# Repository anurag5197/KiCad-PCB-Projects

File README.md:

# KiCad PCB Projects — Anurag Kumar Gupta

A collection of PCB designs created in KiCad as part of my 
electronics engineering coursework and self-learning.

## Projects

### Motor Driver — DRV8833
Dual H-bridge motor driver PCB with PWM control, fault monitoring,
and thermally optimized layout using ground planes and thermal vias.

### USB to UART Converter
USB Type-C to UART converter using CP2102 IC for serial communication
between PC and embedded devices. 36 nets, fully routed.

### DC-DC Boost Converter
Boost converter PCB for stepping up DC voltage. Fully routed,
fabrication-ready design.

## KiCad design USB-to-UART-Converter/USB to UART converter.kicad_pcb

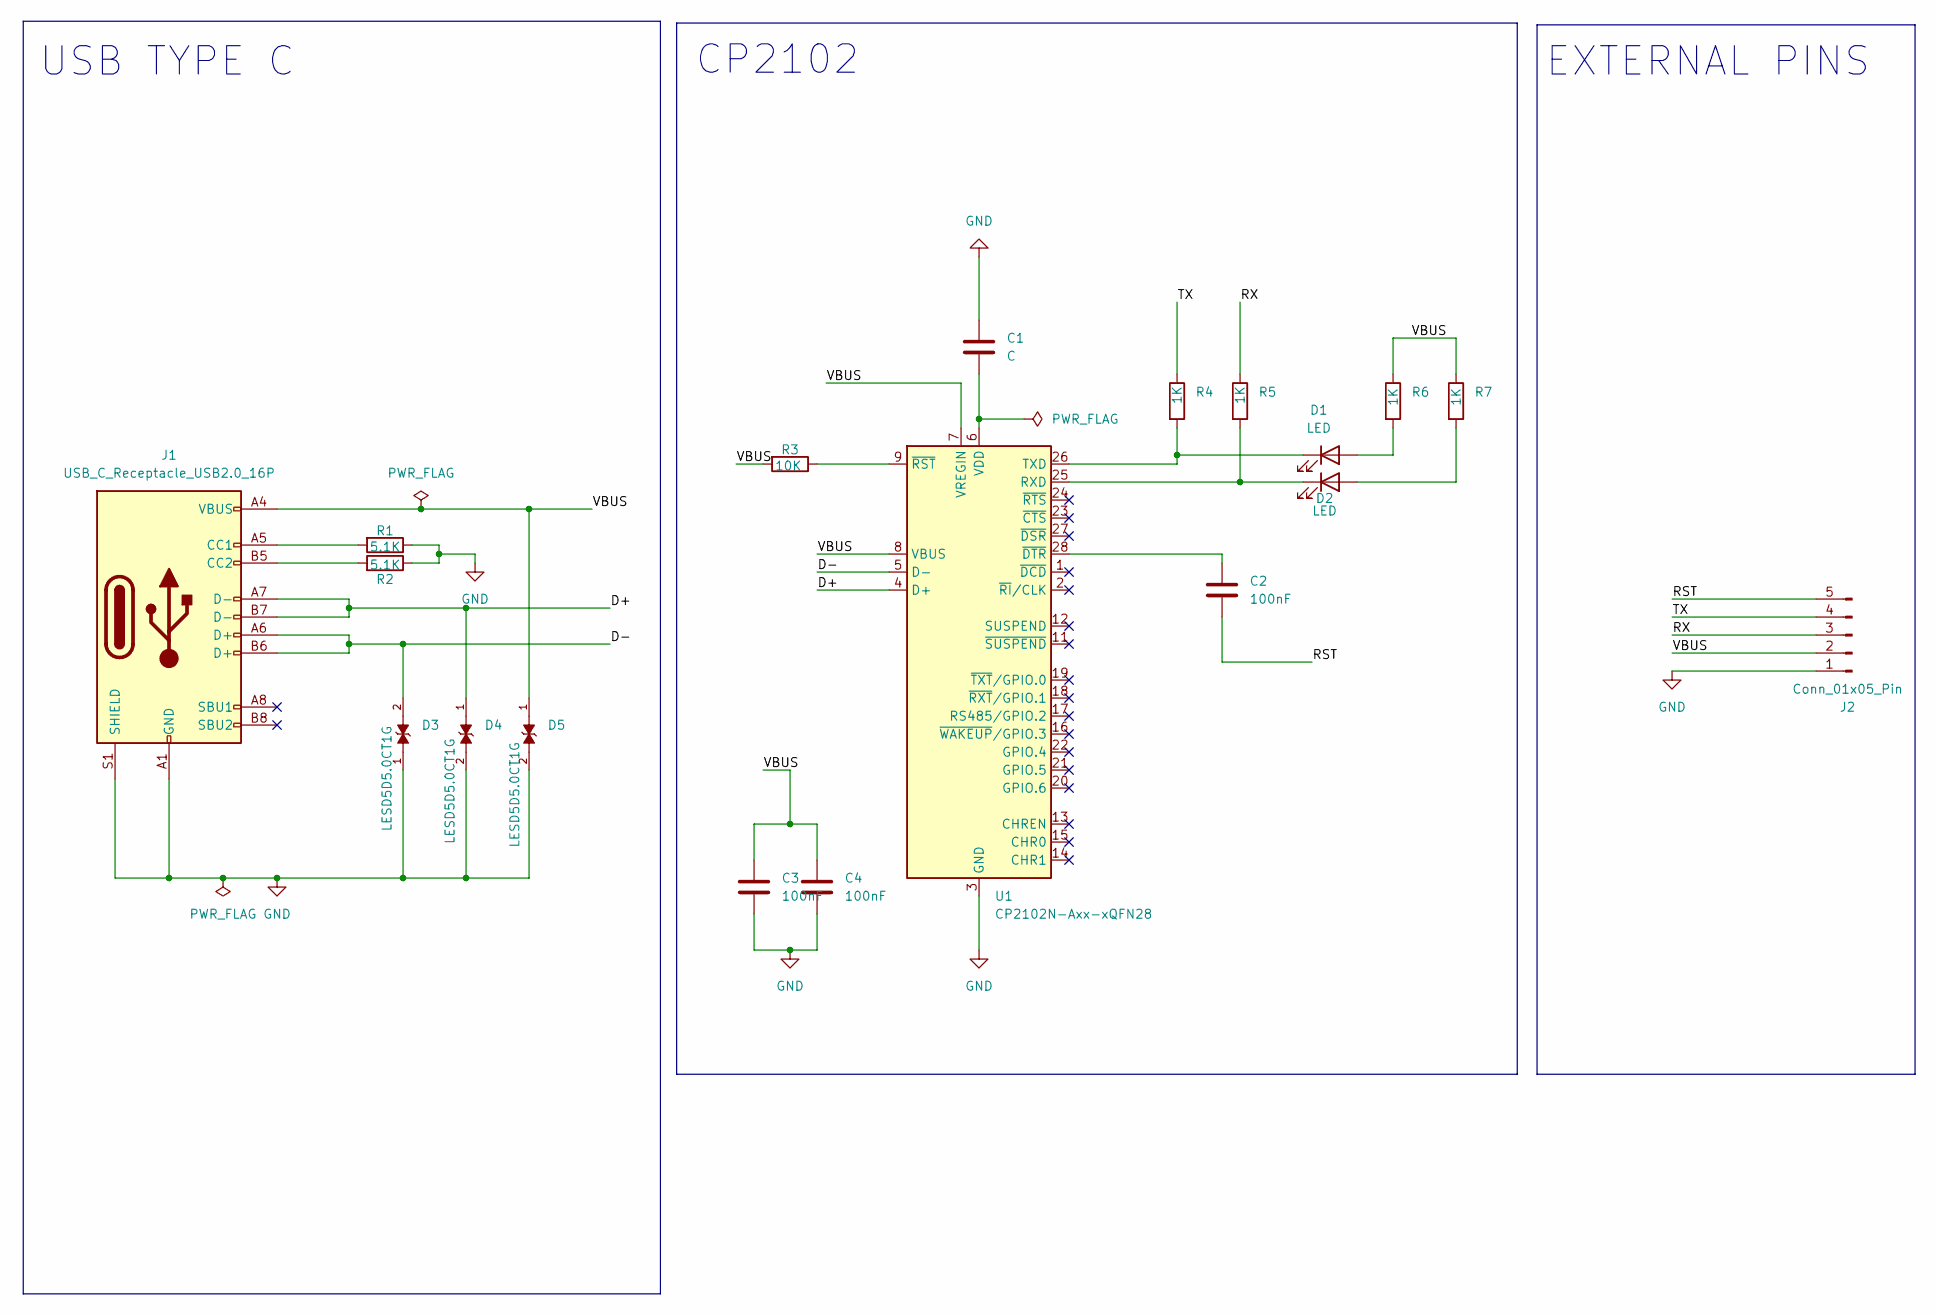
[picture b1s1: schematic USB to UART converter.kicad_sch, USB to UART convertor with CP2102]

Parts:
C1: C; C_0201_0603Metric
C2, C3, C4: 100nF; C_0201_0603Metric
D1, D2: LED; LED_0201_0603Metric
D3, D4, D5: LESD5D5.0CT1G; TVS_LESD5D5.0CT1G; PARTREV O
J1: USB_C_Receptacle_USB2.0_16P; USB_C_Receptacle_HRO_TYPE-C-31-M-12
J2: Conn_01x05_Pin; PinHeader_1x05_P2.54mm_Vertical
R1, R2: 5.1K; R_0201_0603Metric
R3: 10K; R_0201_0603Metric
R4, R5, R6, R7: 1K; R_0201_0603Metric
U1: CP2102N-Axx-xQFN28; QFN-28-1EP_5x5mm_P0.5mm_EP3.35x3.35mm

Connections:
/D+: D4.1, J1.A7 (D-), J1.B7 (D-), U1.4 (D+)
/D-: D3.2, J1.A6 (D+), J1.B6 (D+), U1.5 (D-)
/RST: C2.2, J2.5
/RX: J2.3, R5.1
/TX: J2.4, R4.1
/VBUS: C3.1, C4.1, D5.1, J1.A4 (VBUS), J1.A9 (VBUS), J1.B4 (VBUS), J1.B9 (VBUS), J2.2, R3.2, R6.1, R7.1, U1.7 (VREGIN), U1.8 (VBUS)
GND: C1.1, C3.2, C4.2, D3.1, D4.2, D5.2, J1.A1 (GND), J1.A12 (GND), J1.B1 (GND), J1.B12 (GND), J1.S1 (SHIELD), J2.1, R1.1, R2.1, U1.3 (GND), U1.29 (GND)
unnamed: D1.2 (A), R6.2
unnamed: D1.1 (K), R4.2, U1.26 (TXD)
unnamed: D2.2 (A), R7.2
unnamed: D2.1 (K), R5.2, U1.25 (RXD)
unnamed: J1.A5 (CC1), R1.2
unnamed: J1.B5 (CC2), R2.2
unnamed: C1.2, U1.6 (VDD)
unnamed: C2.1, U1.28 (~DTR)
unnamed: R3.1, U1.9 (~RST)

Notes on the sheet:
CP2102
USB TYPE C
EXTERNAL PINS

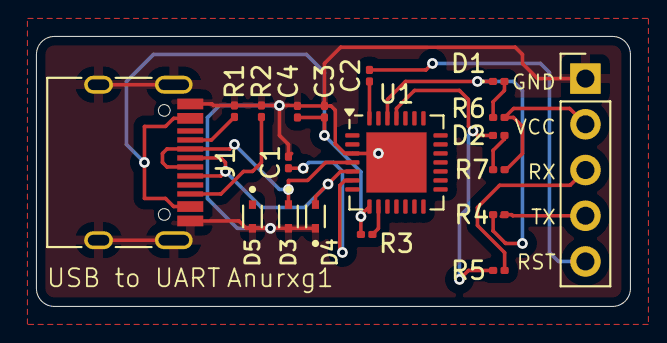
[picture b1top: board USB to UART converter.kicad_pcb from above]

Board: 2 copper layers, 33.0 x 15.0 mm, 19 parts (0 on the bottom side), 16 nets.

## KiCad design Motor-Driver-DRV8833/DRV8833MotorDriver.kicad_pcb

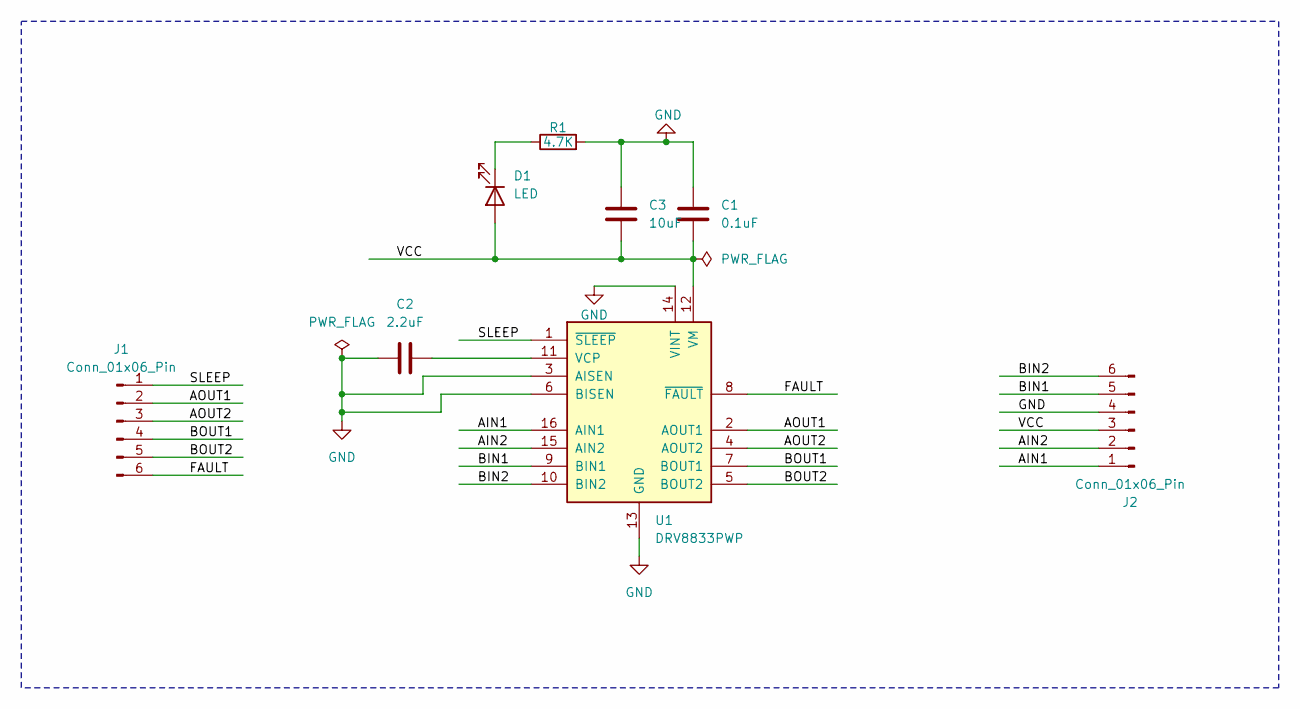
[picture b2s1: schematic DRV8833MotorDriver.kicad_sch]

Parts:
C1: 0.1uF; C_0805_2012Metric
C2: 2.2uF; C_0805_2012Metric
C3: 10uF; CP_EIA-6032-20_AVX-F
D1: LED; LED_0805_2012Metric
J1, J2: Conn_01x06_Pin; PinHeader_1x06_P2.54mm_Vertical
R1: 4.7K; R_0805_2012Metric
U1: DRV8833PWP; HTSSOP-16-1EP_4.4x5mm_P0.65mm_EP3.4x5mm_Mask2.46x2.31mm_The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

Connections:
/AIN1: J2.1, U1.16 (AIN1)
/AIN2: J2.2, U1.15 (AIN2)
/AOUT1: J1.2, U1.2 (AOUT1)
/AOUT2: J1.3, U1.4 (AOUT2)
/BIN1: J2.5, U1.9 (BIN1)
/BIN2: J2.6, U1.10 (BIN2)
/BOUT1: J1.4, U1.7 (BOUT1)
/BOUT2: J1.5, U1.5 (BOUT2)
/FAULT: J1.6, U1.8 (~FAULT)
/SLEEP: J1.1, U1.1 (~SLEEP)
/VCC: C1.2, C3.2, D1.2 (A), J2.3, U1.12 (VM)
GND: C1.1, C2.2, C3.1, J2.4, R1.2, U1.3 (AISEN), U1.6 (BISEN), U1.13 (GND), U1.14 (VINT), U1.17 (GND)
unnamed: D1.1 (K), R1.1
unnamed: C2.1, U1.11 (VCP)

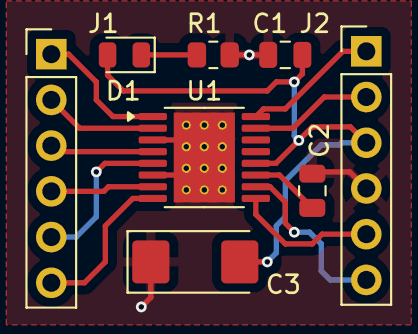
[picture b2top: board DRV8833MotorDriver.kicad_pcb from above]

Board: 2 copper layers, 8 parts (0 on the bottom side), 14 nets.

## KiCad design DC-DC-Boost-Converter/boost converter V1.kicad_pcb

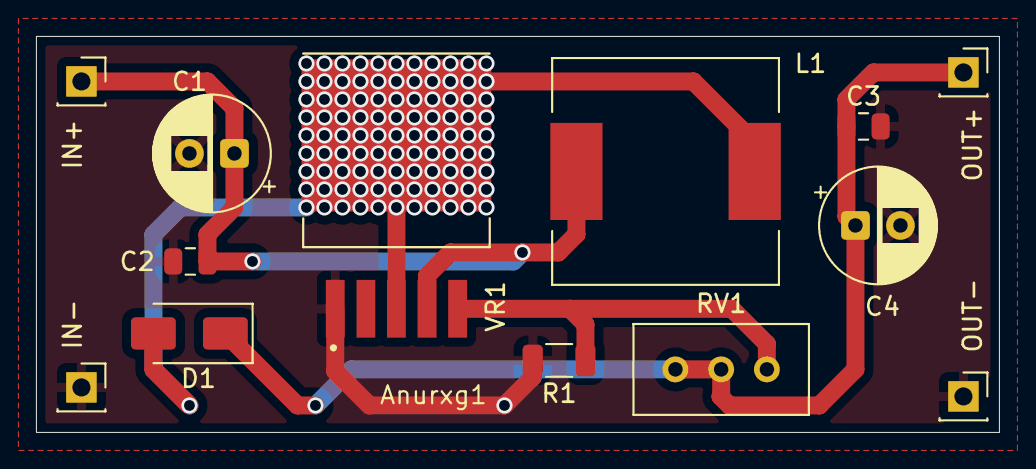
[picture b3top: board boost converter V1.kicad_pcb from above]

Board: 2 copper layers, 53.5 x 22.0 mm, 13 parts (0 on the bottom side), 5 nets.

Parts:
C1: 47uF/50V; CP_Radial_D6.3mm_P2.50mm
C2, C3: 1uF; C_0805_2012Metric
C4: 220uF/50V; CP_Radial_D6.3mm_P2.50mm
D1: SS34; D_SMA
IN+: Conn_01x01_Pin; PinSocket_1x01_P2.54mm_Vertical
IN-: Conn_01x01_Pin; PinSocket_1x01_P2.54mm_Vertical
L1: 33uH; L_12x12mm_H8mm
OUT+: Conn_01x01_Pin; PinSocket_1x01_P2.54mm_Vertical
OUT-: Conn_01x01_Pin; PinSocket_1x01_P2.54mm_Vertical
R1: 1K; R_1206_3216Metric
RV1: 50K; Potentiometer_Bourns_3296W_Vertical
VR1: XL6009; DPAK170P1435X465-6N

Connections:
GND: C1.2, C2.2, C3.2, C4.2, IN-.1, OUT-.1, R1.2, VR1.1 (GND)
unnamed: D1.2 (A), L1.2, VR1.3 (SW), VR1.6 (SW)
unnamed: C3.1, C4.1, D1.1 (K), OUT+.1, RV1.2, RV1.3
unnamed: C1.1, C2.1, IN+.1, L1.1, VR1.4 (VIN)
unnamed: R1.1, RV1.1, VR1.5 (FB)
